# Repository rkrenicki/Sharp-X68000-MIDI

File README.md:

# Sharp-X68000-MIDI
MIDI Output card for Sharp X68000 Computers

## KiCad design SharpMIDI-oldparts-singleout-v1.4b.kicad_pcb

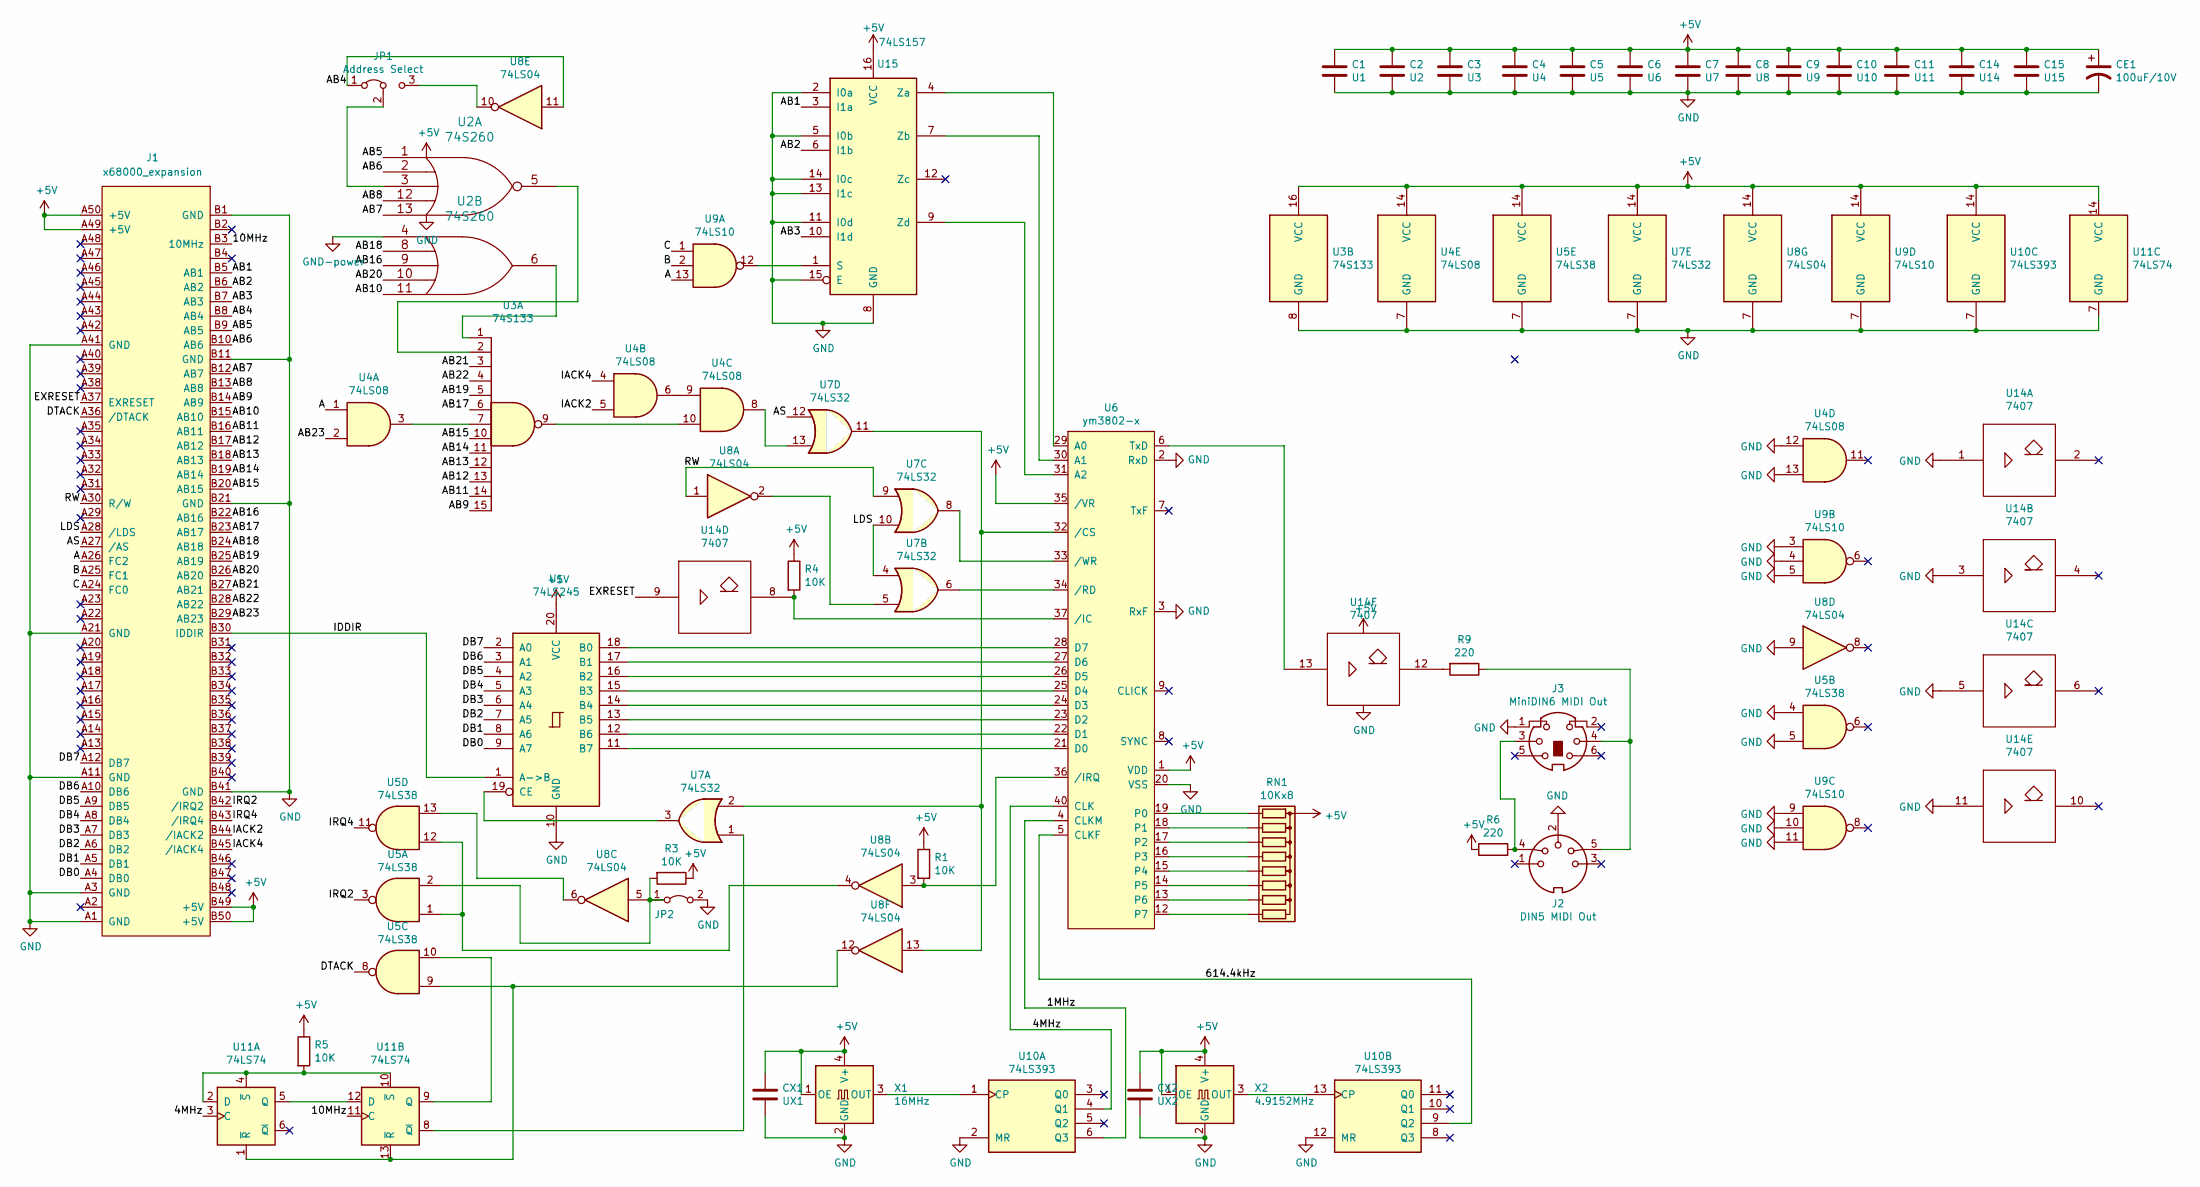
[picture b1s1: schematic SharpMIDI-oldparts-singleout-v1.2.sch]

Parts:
C1: U1; C_Disc_D3.0mm_W2.0mm_P2.50mm
C2: U2; C_Disc_D3.0mm_W2.0mm_P2.50mm
C3: U3; C_Disc_D3.0mm_W2.0mm_P2.50mm
C4: U4; C_Disc_D3.0mm_W2.0mm_P2.50mm
C5: U5; C_Disc_D3.0mm_W2.0mm_P2.50mm
C6: U6; C_Disc_D3.0mm_W2.0mm_P2.50mm
C7: U7; C_Disc_D3.0mm_W2.0mm_P2.50mm
C8: U8; C_Disc_D3.0mm_W2.0mm_P2.50mm
C9: U9; C_Disc_D3.0mm_W2.0mm_P2.50mm
C10: U10; C_Disc_D3.0mm_W2.0mm_P2.50mm
C11: U11; C_Disc_D3.0mm_W2.0mm_P2.50mm
C14: U14; C_Disc_D3.0mm_W2.0mm_P2.50mm
C15: U15; C_Disc_D3.0mm_W2.0mm_P2.50mm
CE1: 100uF/10V; CP_Radial_D5.0mm_P2.50mm
CX1: UX1; C_Disc_D3.0mm_W2.0mm_P2.50mm
CX2: UX2; C_Disc_D3.0mm_W2.0mm_P2.50mm
J1: x68000_expansion
J2: DIN5 MIDI Out; sds-50j
J3: MiniDIN6 MIDI Out; MINI-DIN-6-FULL-SHIELD
JP1: Address Select; PinHeader_1x03_P2.54mm_Vertical
JP2: IRQ Select; PinHeader_1x02_P2.54mm_Vertical
R1, R3, R4, R5: 10K; R_Axial_DIN0204_L3.6mm_D1.6mm_P5.08mm_Horizontal
R6, R9: 220; R_Axial_DIN0204_L3.6mm_D1.6mm_P5.08mm_Horizontal
RN1: 10Kx8; R_Array_SIP9
U1: 74LS245; DIP-20_W7.62mm_LongPads
U2: 74S260; DIP-14_W7.62mm_LongPads
U3: 74S133; DIP-16_W7.62mm_LongPads
U4: 74LS08; DIP-14_W7.62mm_LongPads
U5: 74LS38; DIP-14_W7.62mm_LongPads
U6: ym3802-x; DIP-40_W15.24mm_LongPads
U7: 74LS32; DIP-14_W7.62mm_LongPads
U8: 74LS04; DIP-14_W7.62mm_LongPads
U9: 74LS10; DIP-14_W7.62mm_LongPads
U10: 74LS393; DIP-14_W7.62mm_LongPads
U11: 74LS74; DIP-14_W7.62mm_LongPads
U14: 7407; DIP-14_W7.62mm_LongPads
U15: 74LS157; DIP-16_W7.62mm_LongPads
X1: 16MHz; Oscillator_DIP-14_LargePads-dualfootprint
X2: 4.9152MHz; Oscillator_DIP-14_LargePads-dualfootprint

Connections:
+5V: C1.1, C2.1, C3.1, C4.1, C5.1, C6.1, C7.1, C8.1, C9.1, C10.1, C11.1, C14.1, C15.1, CE1.1, CX1.1, CX2.1, J1.A49 (+5V), J1.A50 (+5V), J1.B49 (+5V), J1.B50 (+5V), R1.1, R3.1, R4.1, R5.1, R6.1, RN1.1 (common), U1.20 (VCC), U2.14 (VCC), U3.16 (VCC), U4.14 (VCC), U5.14 (VCC), U6.1 (VDD), U6.35 (/VR), U7.14 (VCC), U8.14 (VCC), U9.14 (VCC), U10.14 (VCC), U11.14 (VCC), U14.14 (Vcc), U15.16 (VCC), X1.1 (OE), X1.4 (V+), X2.1 (OE), X2.4 (V+)
/1MHz: U6.4 (CLKM), U10.6 (Q3)
/4MHz: U6.40 (CLK), U10.4 (Q1), U11.3 (C)
/10MHz: J1.B3 (10MHz), U11.11 (C)
/614.4kHz: U6.5 (CLKF), U10.9 (Q2)
/A: J1.A26 (FC2), U4.1, U9.13
/AB1: J1.B5 (AB1), U15.3 (I1a)
/AB2: J1.B6 (AB2), U15.6 (I1b)
/AB3: J1.B7 (AB3), U15.10 (I1d)
/AB4: J1.B8 (AB4), JP1.1 (A), U8.11
/AB5: J1.B9 (AB5), U2.1 (I0)
/AB6: J1.B10 (AB6), U2.2 (I1)
/AB7: J1.B12 (AB7), U2.13 (I4)
/AB8: J1.B13 (AB8), U2.12 (I3)
/AB9: J1.B14 (AB9), U3.15
/AB10: J1.B15 (AB10), U2.11 (I4)
/AB11: J1.B16 (AB11), U3.14
/AB12: J1.B17 (AB12), U3.13
/AB13: J1.B18 (AB13), U3.12
/AB14: J1.B19 (AB14), U3.11
/AB15: J1.B20 (AB15), U3.10
/AB16: J1.B22 (AB16), U2.9 (I2)
/AB17: J1.B23 (AB17), U3.6
/AB18: J1.B24 (AB18), U2.8 (I1)
/AB19: J1.B25 (AB19), U3.5
/AB20: J1.B26 (AB20), U2.10 (I3)
/AB21: J1.B27 (AB21), U3.3
/AB22: J1.B28 (AB22), U3.4
/AB23: J1.B29 (AB23), U4.2
/AS: J1.A27 (/AS), U7.12
/B: J1.A25 (FC1), U9.2
/C: J1.A24 (FC0), U9.1
/DB0: J1.A4 (DB0), U1.9 (A7)
/DB1: J1.A5 (DB1), U1.8 (A6)
/DB2: J1.A6 (DB2), U1.7 (A5)
/DB3: J1.A7 (DB3), U1.6 (A4)
/DB4: J1.A8 (DB4), U1.5 (A3)
/DB5: J1.A9 (DB5), U1.4 (A2)
/DB6: J1.A10 (DB6), U1.3 (A1)
/DB7: J1.A12 (DB7), U1.2 (A0)
/DTACK: J1.A36 (/DTACK), U5.8
/EXRESET: J1.A37 (EXRESET), U14.9
/IACK2: J1.B44 (/IACK2), U4.5
/IACK4: J1.B45 (/IACK4), U4.4
/IDDIR: J1.B30 (IDDIR), U1.1 (A->B)
/IRQ2: J1.B42 (/IRQ2), U5.3
/IRQ4: J1.B43 (/IRQ4), U5.11
/LDS: J1.A28 (/LDS), U7.4, U7.10
/RW: J1.A30 (R/W), U7.9, U8.1
unnamed: J2.4, J3.3, R6.2
unnamed: J2.5, J3.4, R9.1
unnamed: JP1.2 (C), U2.3 (I2)
unnamed: JP1.3 (B), U8.10
unnamed: JP2.1 (A), R3.2, U5.2, U8.5
unnamed: R1.2, U6.36 (/IRQ), U8.3
unnamed: R4.2, U6.37 (/IC), U14.8
unnamed: R5.2, U11.2 (D), U11.4 (~S), U11.10 (~S)
unnamed: R9.2, U14.12
unnamed: RN1.2 (R1), U6.19 (P0)
unnamed: RN1.3 (R2), U6.18 (P1)
unnamed: RN1.4 (R3), U6.17 (P2)
unnamed: RN1.5 (R4), U6.16 (P3)
unnamed: RN1.6 (R5), U6.15 (P4)
unnamed: RN1.7 (R6), U6.14 (P5)
unnamed: RN1.8 (R7), U6.13 (P6)
unnamed: RN1.9 (R8), U6.12 (P7)
unnamed: U1.11 (B7), U6.21 (D0)
unnamed: U1.12 (B6), U6.22 (D1)
unnamed: U1.13 (B5), U6.23 (D2)
unnamed: U1.14 (B4), U6.24 (D3)
unnamed: U1.15 (B3), U6.25 (D4)
unnamed: U1.16 (B2), U6.26 (D5)
unnamed: U1.17 (B1), U6.27 (D6)
unnamed: U1.18 (B0), U6.28 (D7)
unnamed: U1.19 (CE), U7.3
unnamed: U2.5 (O), U3.2
unnamed: U2.6 (O), U3.1
unnamed: U3.7, U4.3
unnamed: U3.9, U4.10
unnamed: U4.6, U4.9
unnamed: U4.8, U7.13
unnamed: U5.1, U5.12, U8.4
unnamed: U5.13, U8.6
unnamed: U6.32 (/CS), U7.2, U7.11, U8.13
unnamed: U6.33 (/WR), U7.8
unnamed: U6.34 (/RD), U7.6
unnamed: U7.5, U8.2
unnamed: U10.1 (CP), X1.3 (OUT)
unnamed: U10.13 (CP), X2.3 (OUT)
unnamed: U5.9, U8.12, U11.1 (~R), U11.13 (~R)
unnamed: U7.1, U11.8 (~Q)
unnamed: U5.10, U11.9 (Q)
unnamed: U11.5 (Q), U11.12 (D)
unnamed: U6.6 (TxD), U14.13
unnamed: U9.12, U15.1 (S)
unnamed: U6.29 (A0), U15.4 (Za)
unnamed: U6.30 (A1), U15.7 (Zb)
unnamed: U6.31 (A2), U15.9 (Zd)

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
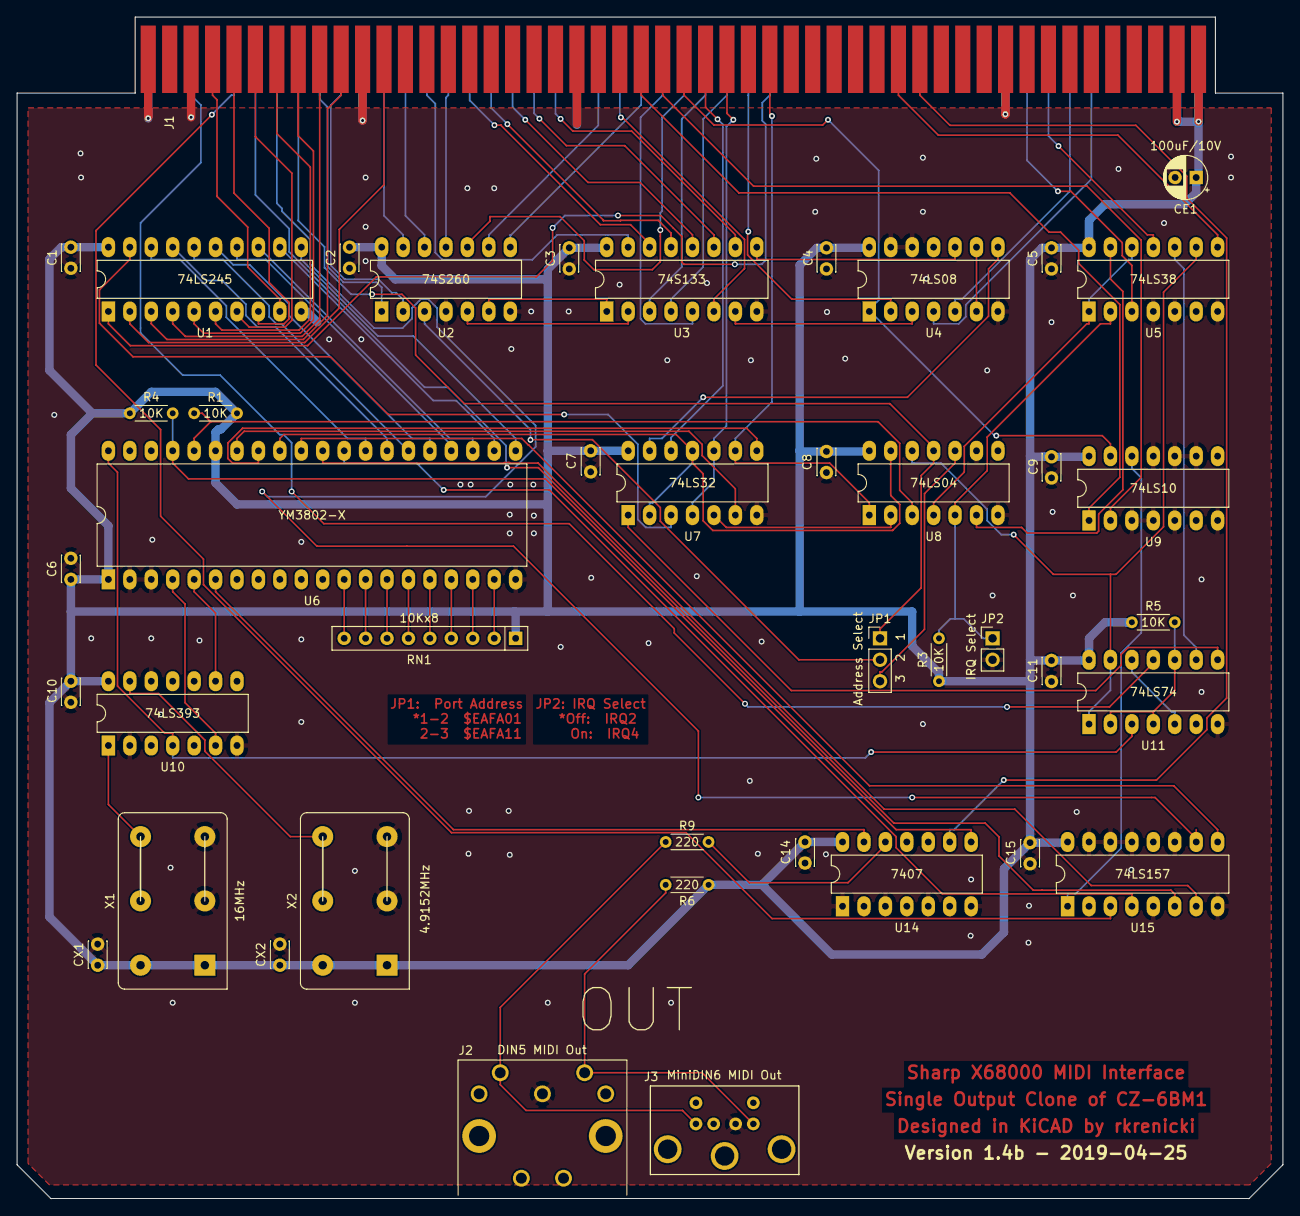
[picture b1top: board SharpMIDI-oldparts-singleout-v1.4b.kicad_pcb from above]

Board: 2 copper layers, 150.0 x 140.0 mm, 43 parts (0 on the bottom side), 99 nets.
